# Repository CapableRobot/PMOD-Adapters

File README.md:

# PMOD Adapters

Designed by [Capable Robot Components](http://capablerobot.com).  Follow us on [Twitter](http://twitter.com/capablerobot) for product announcements and updates.

---

This repository contains schematics, layout, and bill of materials for various PMOD adapters and interfaces.  This currently includes:

* 2019-01-30 : [CRBFH0 - LED Debug](boards/LED-Debug)
* 2019-01-30 : [CR6QEG - PMOD Debug](boards/Debug)
* 2018-09-13 : [CR7CSZ - BeagleWire to PMOD](boards/BeagleWire) 
* 2018-09-13 : [CRRYEK - BeagleWire to Debug PMOD](boards/BeagleWire-Debug)

Additional designed will be added to this repository over time.  

| **Type** | **License** |
| --- | --- |
| Hardware | Copyright Capable Robot Components 2018 <br><br>This documentation describes Open Hardware and is licensed under the [CERN OHL v1.2 or later](https://www.ohwr.org/licenses/cern-ohl/license_versions/v1.2). <br/><br/> You may redistribute and modify this documentation under the terms of the CERN OHL v.1.2.  This documentation is distributed WITHOUT ANY EXPRESS OR IMPLIED WARRANTY, INCLUDING OF MERCHANTABILITY, SATISFACTORY QUALITY AND FITNESS FOR A PARTICULAR PURPOSE. Please see the CERN OHL v.1.2 for applicable conditions |
| Software | [MIT License](LICENSE.txt) |

More detailed information about the CERN License is available in the [license](license) folder and on the [CERN website](https://www.ohwr.org/projects/cernohl/wiki).

---

### [CRBFH0] LED Debug

|  |  |
| :-------------: | :-------------: |
| **Top Rendering**    | **Bottom Rendering** |

This PCB allows a single PMOD to control 64 LEDs via a 4:16 address decoder and 4 mask control signals.  It was originally designed by H.Poetzl as part of the [Apertus project](https://www.apertus.org/pmod-debug).  Changes made to this version are:

- Changed 0402 resistors to 0603 packages.
- Changed the N channel MOSFETs from SC75 to SOT23 packages. 
- PCB layout changes to accommodate the larger components.

No schematic changes were made, meaning the PMOD interface is identical.

This board can be ordered at [OSH Park](https://oshpark.com/shared_projects/n7GHOesv) and costs $6.75 for a set of 3.

---

### [CR6QEG] PMOD Debug

|  |  |
| :-------------: | :-------------: |
| **Top Rendering**    | **Bottom Rendering** |

This PCB adapts allows for probing of signals between an FPGA development board an a PMOD peripheral.  

A 2x6 right angle male header should be installed in the `FPGA` header and a 2x6 right angle female header should be installed into the `PMOD` header.

This board can be ordered at [OSH Park](https://oshpark.com/shared_projects/YEDBhzJa) and costs $3.20 for a set of 3.

---

### [CR7CSZ] BeagleWire to PMOD

|  |  |
| :-------------: | :-------------: |
| **Top Rendering**    | **Bottom Rendering** |

This PCB adapts standard PMOD peripherals to the BeagleWire PMOD connectors.  

The BeagleWire has a reversed pinout wherein the Power and Ground are on the right side of the connector (as you face a female PMOD on the BeagleWire) while all other PMOD hosts have the Power and Ground on the left side of the connector.

A 2x6 right angle male header should be installed in the `BEAGLE` header and a 2x6 right angle female header should be installed into the `PMOD` header.

This board can be ordered at [OSH Park](https://oshpark.com/shared_projects/sm0OcuML) and costs $2.40 for a set of 3.

---

### [CRRYEK] BeagleWire to Debug PMOD

|  |  |
| :-------------: | :-------------: |
| **Top Rendering**    | **Bottom Rendering** |

This PCB adapts standard PMOD peripherals to the BeagleWire PMOD connectors.  It is similar to the CR7CSZ version but adds an additional 2x6 header (standard PMOD pinout) to aid in probing and debugging signals between the BeagleWire and the PMOD peripheral.

A 2x6 right angle male header should be installed in the `BEAGLE` header and a 2x6 right angle female header should be installed into the `PMOD` header.

This board can be ordered at [OSH Park](https://oshpark.com/shared_projects/SsbzeQ1o) and costs $3.20 for a set of 3.

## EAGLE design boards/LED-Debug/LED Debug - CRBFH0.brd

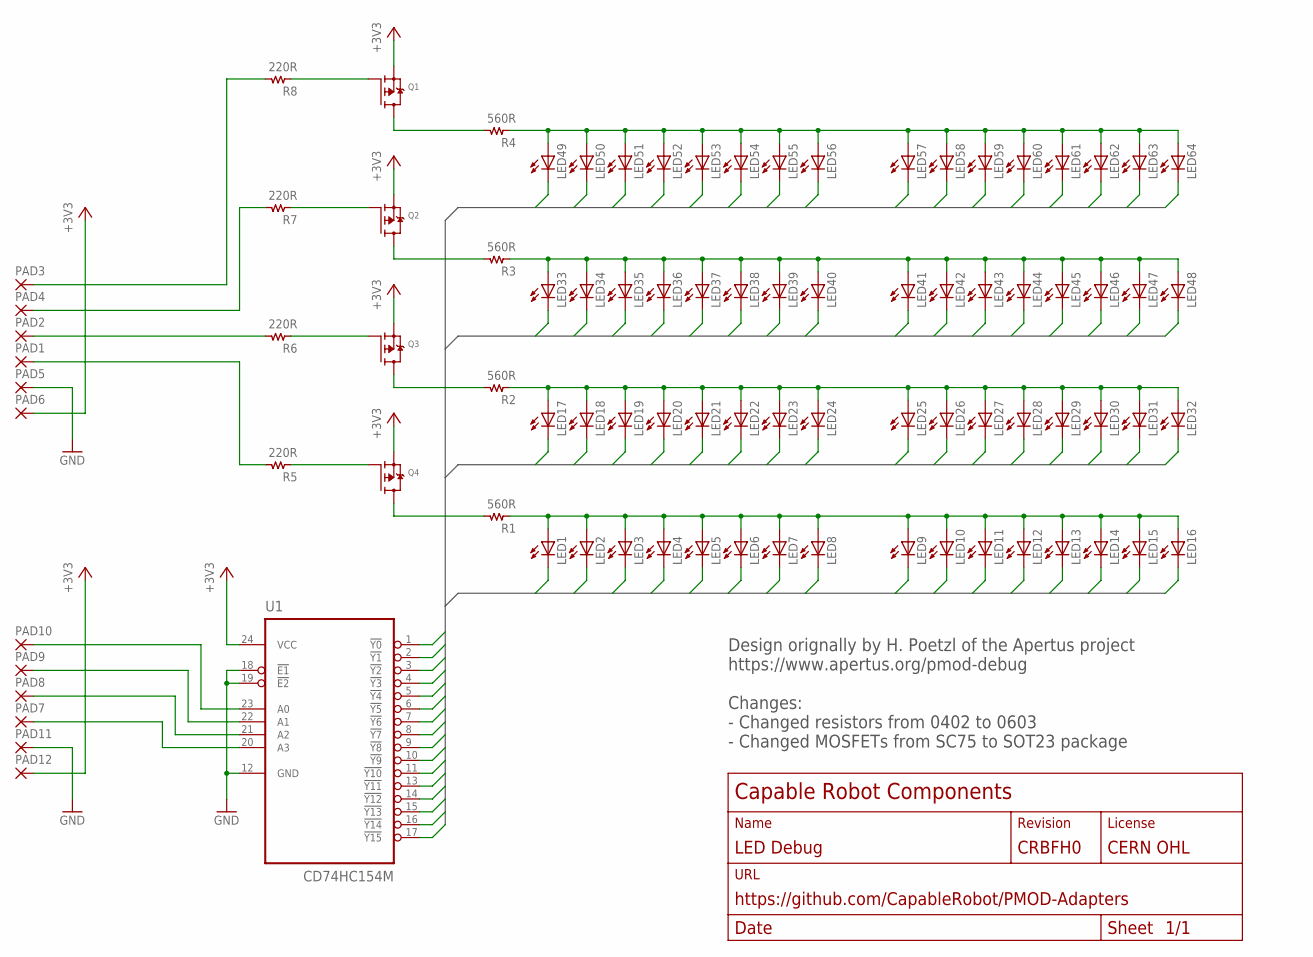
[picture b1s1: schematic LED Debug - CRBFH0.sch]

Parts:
LED1, LED2, LED3, LED4, LED5, LED6, LED7, LED8, LED9, LED10, LED11, LED12, LED13, LED14, LED15, LED16, LED17, LED18, LED19, LED20, LED21, LED22, LED23, LED24, LED25, LED26, LED27, LED28, LED29, LED30, LED31, LED32, LED33, LED34, LED35, LED36, LED37, LED38, LED39, LED40, LED41, LED42, LED43, LED44, LED45, LED46, LED47, LED48, LED49, LED50, LED51, LED52, LED53, LED54, LED55, LED56, LED57, LED58, LED59, LED60, LED61, LED62, LED63, LED64: LEDCHIP-LED0603; CHIP-LED0603
PAD1, PAD2, PAD3, PAD4, PAD5, PAD6, PAD7, PAD8, PAD9, PAD10, PAD11, PAD12: SMD2HR; SMD1.27-3.175HR
Q1, Q2, Q3, Q4: MOSFET-P; SOT23-R
R1, R2, R3, R4: 560R; 0603
R5, R6, R7, R8: 220R; 0603
U1: CD74HC154M; SOIC127P1030X265-24N

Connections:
+3V3: PAD6.1, PAD12.1, Q1.2 (S), Q2.2 (S), Q3.2 (S), Q4.2 (S), U1.24 (VCC)
C0: LED1.C, LED17.C, LED33.C, LED49.C, U1.1 (!Y0)
C1: LED2.C, LED18.C, LED34.C, LED50.C, U1.2 (!Y1)
C2: LED3.C, LED19.C, LED35.C, LED51.C, U1.3 (!Y2)
C3: LED4.C, LED20.C, LED36.C, LED52.C, U1.4 (!Y3)
C4: LED5.C, LED21.C, LED37.C, LED53.C, U1.5 (!Y4)
C5: LED6.C, LED22.C, LED38.C, LED54.C, U1.6 (!Y5)
C6: LED7.C, LED23.C, LED39.C, LED55.C, U1.7 (!Y6)
C7: LED8.C, LED24.C, LED40.C, LED56.C, U1.8 (!Y7)
C8: LED9.C, LED25.C, LED41.C, LED57.C, U1.9 (!Y8)
C9: LED10.C, LED26.C, LED42.C, LED58.C, U1.10 (!Y9)
C10: LED11.C, LED27.C, LED43.C, LED59.C, U1.11 (!Y10)
C11: LED12.C, LED28.C, LED44.C, LED60.C, U1.13 (!Y11)
C12: LED13.C, LED29.C, LED45.C, LED61.C, U1.14 (!Y12)
C13: LED14.C, LED30.C, LED46.C, LED62.C, U1.15 (!Y13)
C14: LED15.C, LED31.C, LED47.C, LED63.C, U1.16 (!Y14)
C15: LED16.C, LED32.C, LED48.C, LED64.C, U1.17 (!Y15)
GND: PAD5.1, PAD11.1, U1.12 (GND), U1.18 (!E1), U1.19 (!E2)
unnamed: LED1.A, LED2.A, LED3.A, LED4.A, LED5.A, LED6.A, LED7.A, LED8.A, LED9.A, LED10.A, LED11.A, LED12.A, LED13.A, LED14.A, LED15.A, LED16.A, R1.1
unnamed: LED17.A, LED18.A, LED19.A, LED20.A, LED21.A, LED22.A, LED23.A, LED24.A, LED25.A, LED26.A, LED27.A, LED28.A, LED29.A, LED30.A, LED31.A, LED32.A, R2.1
unnamed: LED33.A, LED34.A, LED35.A, LED36.A, LED37.A, LED38.A, LED39.A, LED40.A, LED41.A, LED42.A, LED43.A, LED44.A, LED45.A, LED46.A, LED47.A, LED48.A, R3.1
unnamed: LED49.A, LED50.A, LED51.A, LED52.A, LED53.A, LED54.A, LED55.A, LED56.A, LED57.A, LED58.A, LED59.A, LED60.A, LED61.A, LED62.A, LED63.A, LED64.A, R4.1
unnamed: Q1.3 (D), R4.2
unnamed: Q2.3 (D), R3.2
unnamed: Q4.3 (D), R1.2
unnamed: Q3.3 (D), R2.2
unnamed: Q1.1 (G), R8.1
unnamed: Q2.1 (G), R7.1
unnamed: Q4.1 (G), R5.1
unnamed: Q3.1 (G), R6.1
unnamed: PAD10.1, U1.23 (A0)
unnamed: PAD9.1, U1.22 (A1)
unnamed: PAD8.1, U1.21 (A2)
unnamed: PAD7.1, U1.20 (A3)
unnamed: PAD1.1, R5.2
unnamed: PAD2.1, R6.2
unnamed: PAD3.1, R8.2
unnamed: PAD4.1, R7.2

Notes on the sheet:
Design orignally by H. Poetzl of the Apertus project https://www.apertus.org/pmod-debug Changes: - Changed resistors from 0402 to 0603 - Changed MOSFETs from SC75 to SOT23 package

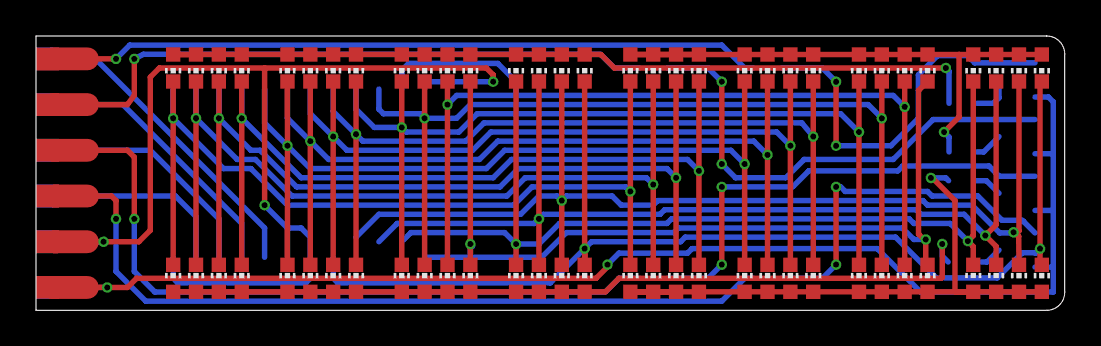
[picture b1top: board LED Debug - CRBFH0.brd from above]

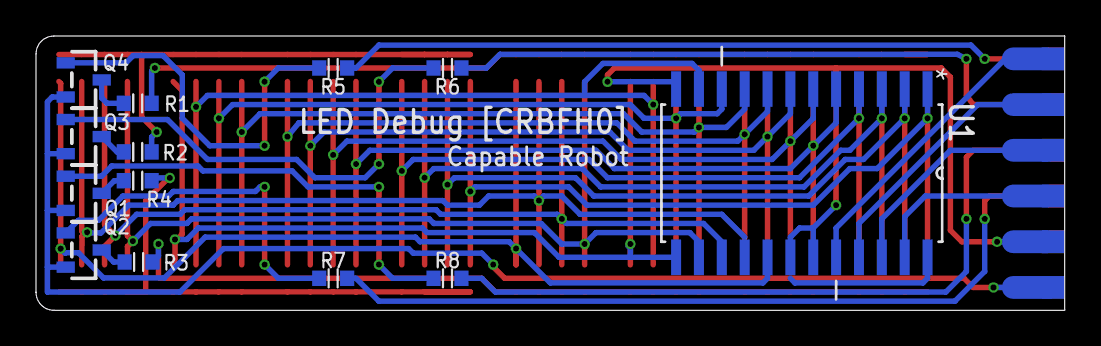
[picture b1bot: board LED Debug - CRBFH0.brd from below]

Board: 2 copper layers, 57.1 x 15.2 mm, 89 parts (19 on the bottom side), 38 nets.

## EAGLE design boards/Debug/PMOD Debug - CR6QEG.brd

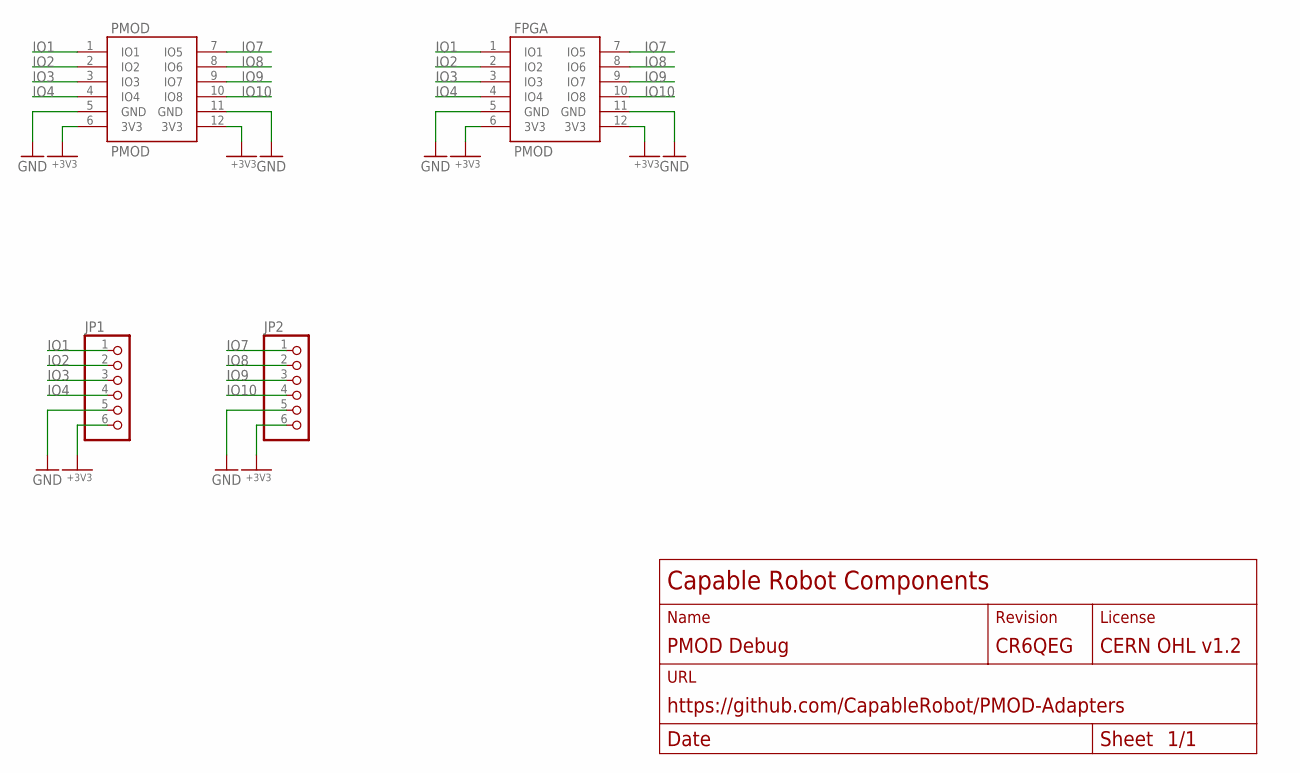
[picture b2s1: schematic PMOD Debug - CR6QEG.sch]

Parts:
FPGA: PMOD-PERIPH; HDRRA12W64P254_2X6_1524X254X556B
JP1, JP2: PINHD-1X6; 1X06
PMOD: PMOD-HOST; HDRRAR12W64P254_2X6_1524X736X556B

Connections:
+3V3: FPGA.6 (3V3), FPGA.12 (3V3), JP1.6, JP2.6, PMOD.6 (3V3), PMOD.12 (3V3)
GND: FPGA.5 (GND), FPGA.11 (GND), JP1.5, JP2.5, PMOD.5 (GND), PMOD.11 (GND)
IO1: FPGA.1 (IO1), JP1.1, PMOD.1 (IO1)
IO2: FPGA.2 (IO2), JP1.2, PMOD.2 (IO2)
IO3: FPGA.3 (IO3), JP1.3, PMOD.3 (IO3)
IO4: FPGA.4 (IO4), JP1.4, PMOD.4 (IO4)
IO7: FPGA.7 (IO5), JP2.1, PMOD.7 (IO5)
IO8: FPGA.8 (IO6), JP2.2, PMOD.8 (IO6)
IO9: FPGA.9 (IO7), JP2.3, PMOD.9 (IO7)
IO10: FPGA.10 (IO8), JP2.4, PMOD.10 (IO8)

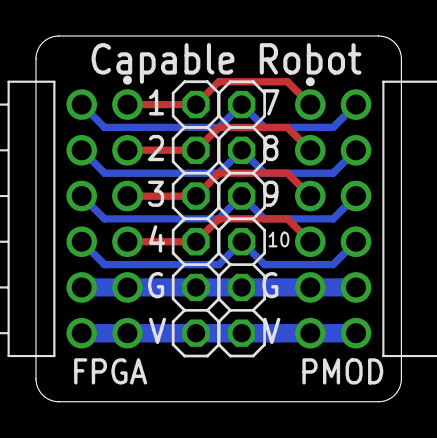
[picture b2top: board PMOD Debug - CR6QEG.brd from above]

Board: 2 copper layers, 20.3 x 20.3 mm, 4 parts (0 on the bottom side), 10 nets.

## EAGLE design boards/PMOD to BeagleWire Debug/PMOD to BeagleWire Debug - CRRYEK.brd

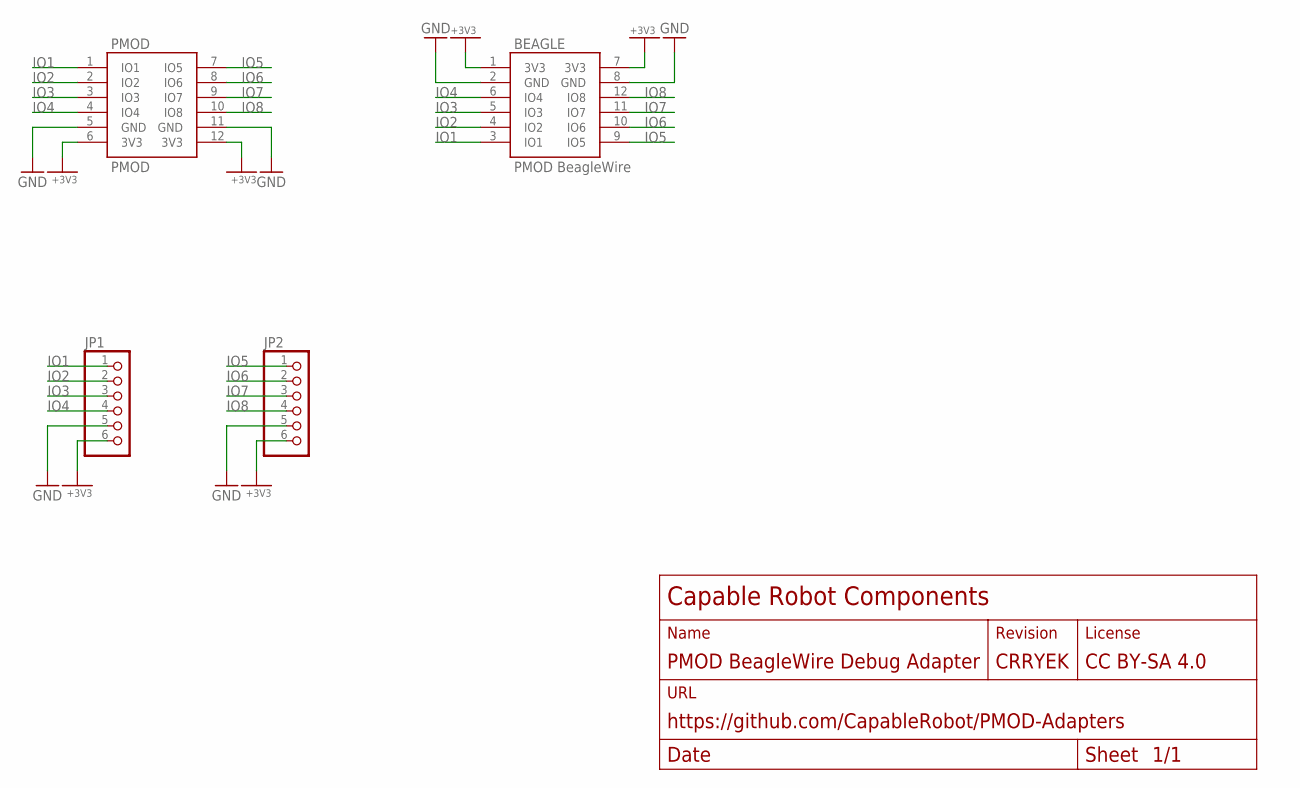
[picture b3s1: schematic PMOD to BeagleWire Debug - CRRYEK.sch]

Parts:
BEAGLE: PMOD-BEAGLEWIRE; HDRRA12W64P254_2X6_1524X254X556B
JP1, JP2: PINHD-1X6; 1X06
PMOD: PMOD-HOST; HDRRAR12W64P254_2X6_1524X736X556B

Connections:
+3V3: BEAGLE.1 (3V3), BEAGLE.7 (3V3), JP1.6, JP2.6, PMOD.6 (3V3), PMOD.12 (3V3)
GND: BEAGLE.2 (GND), BEAGLE.8 (GND), JP1.5, JP2.5, PMOD.5 (GND), PMOD.11 (GND)
IO1: BEAGLE.3 (IO1), JP1.1, PMOD.1 (IO1)
IO2: BEAGLE.4 (IO2), JP1.2, PMOD.2 (IO2)
IO3: BEAGLE.5 (IO3), JP1.3, PMOD.3 (IO3)
IO4: BEAGLE.6 (IO4), JP1.4, PMOD.4 (IO4)
IO5: BEAGLE.9 (IO5), JP2.1, PMOD.7 (IO5)
IO6: BEAGLE.10 (IO6), JP2.2, PMOD.8 (IO6)
IO7: BEAGLE.11 (IO7), JP2.3, PMOD.9 (IO7)
IO8: BEAGLE.12 (IO8), JP2.4, PMOD.10 (IO8)

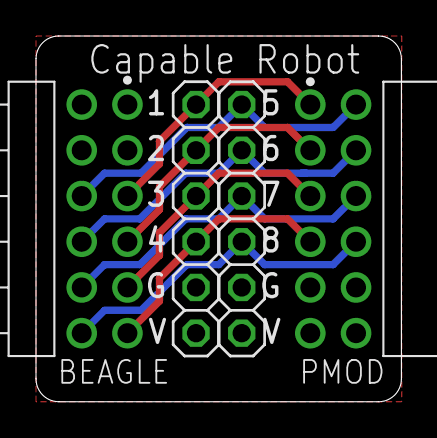
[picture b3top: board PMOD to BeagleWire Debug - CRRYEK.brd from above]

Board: 2 copper layers, 20.3 x 20.3 mm, 4 parts (0 on the bottom side), 10 nets.

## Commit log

2018-09-14 Adding PMOD to BeagleWire PMOD adapter
2018-09-14 Adding PMOD to BeagleWire PMOD (with debug header) adapter
2018-09-14 Change file and folder names
2018-09-14 Fix links in README
2018-09-14 Added OSH Park image links
2018-09-28 Change license from CC BY-SA to CERN OHL
2018-09-28 Change URL of CERN license
2019-01-03 Adding standard PMOD debug
2019-01-03 Change font
2019-01-03 Resize board images
2019-01-03 Added text about standard PMOD debug board
2019-01-03 Added LED debug board, modified from Apertus project LED debug board
2019-01-03 Update readme with info and links to LED Debug PCB
2019-01-03 Added migen software for LED Debug PMOD
2019-01-03 Format changes
2019-01-03 Fix link
2019-01-03 Added MIT license for software
2019-01-03 Updat readme

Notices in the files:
boards/Debug/PMOD Debug - CR6QEG.sch:
LICENSE: CERN OHL v1.2
boards/PMOD to BeagleWire Debug/PMOD to BeagleWire Debug - CRRYEK.sch:
LICENSE: CC BY-SA 4.0
parts and their libraries:
microbuilder: This work is placed in the public domain, and may be freely used for commercial and non-commercial work with the following conditions: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
